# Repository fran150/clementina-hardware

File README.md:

# Clementina Hardware

KiCad 9 schematic and board for Clementina, a 3.3 V homebrew computer built
around a W65C02S CPU. A Raspberry Pi Pico 2 W, called MIA, runs the machine: it
generates the CPU clock, boots the kernel, and provides video, audio, storage
and input.

Status: the rev 1 schematic is complete and ERC-clean, and the rev 1 board is
laid out, fully routed and DRC-clean. The first build is planned on
protoboard, using the same parts as the board.

## Opening the project

Open `clementina-hardware.kicad_pro` in KiCad 9.

- `clementina.kicad_sym` (listed in `sym-lib-table`) holds the parts KiCad's
  own libraries lack, currently the AS6C62256 SRAM.
- The W65C02S and W65C22S symbols come from KiCad's Plugin and Content Manager
  (library `PCM_65xx-library`). The schematic carries copies, so it opens
  without that library. Install it to keep ERC's library check clean.
- One ERC item is excluded on purpose: the Pico's AGND tied to GND. The ADC is
  unused, and the Pico datasheet allows the join.
- `clementina-hardware.kicad_dru` holds one custom DRC rule: the audio jack's
  barrel hangs over the board edge on purpose, so its silkscreen outline may
  cross the edge.
- DRC shows one warning, and it is expected: the Pico footprint "does not
  match the copy in the library". The library's antenna keep-out lists 32
  copper layers, and a 2-layer board keeps only two of them.

Sheets:

| Sheet | Contents |
| --- | --- |
| `clementina-hardware.kicad_sch` (A3) | CPU, VIA, RAM, MIA, IRQ and reset circuits, expansion headers, user port, audio output, microSD, power and decoupling |
| `CS Logic.kicad_sch` | Address decoding (74AC138 x2, 74AC08, two gates of the 74AC00) |
| `OE_RW_PHI2_Sync.kicad_sch` | Read and write strobes: `~OE` from R/W, `~WE` qualified by PHI2 (two gates of the 74AC00) |

## Architecture

| Part | Role |
| --- | --- |
| W65C02S (U1) | CPU. MIA drives PHI2: 1.2 MHz by default, up to 8 MHz. |
| AS6C62256 (U4) | 32 KB base RAM |
| AS6C4008 (U2) | 512 KB extended RAM, seen through a 16 KB window |
| W65C22S (U3) | VIA. Port A selects the extended RAM bank; port B and CA/CB go to the user port. |
| Raspberry Pi Pico 2 W (A1) | MIA: clock, boot loader, video over Wi-Fi, audio, microSD, input, reset |
| 74AC138 x2, 74AC08, 74AC00 | Glue logic (see [Glue logic timing](#glue-logic-timing)) |

Memory map:

| Range | Device |
| --- | --- |
| `$0000-$7FFF` | Base RAM |
| `$8000-$BFFF` | Extended RAM window (32 banks, selected by VIA PA0-PA4) |
| `$C000-$DFFF` | I/O: eight 1 KB slots. Slot 0 (`$C000`) is the VIA; slots 1-7 go to the expansion headers. |
| `$E000-$FFFF` | MIA (registers at `$FFE0-$FFFF`) |

MIA's pins:

| GPIO | Signal |
| --- | --- |
| GP0-GP3 | microSD (SPI0: MISO, CS, SCK, MOSI) |
| GP4, GP5 | Audio left and right (PWM) |
| GP6 | MIA chip select |
| GP7 | R/W |
| GP8-GP15 | D0-D7 |
| GP16-GP20 | A0-A4 |
| GP21 | PHI2 |
| GP22 | IRQ |
| GP26 | RESB (MIA holds the CPU and VIA in reset) |
| GP27 | Reset request from the RESET button |
| GP28 | Unused |

### Glue logic timing

The glue logic is 74AC, not 74HC, because 74HC is slow at 3.3 V (roughly
13 ns per gate typical, up to about 30 ns). Two places depend on it:

- **Write strobe.** `~WE = NAND(PHI2, ~OE)` in one 74AC00 gate, so `~WE`
  rises within about 10 ns of PHI2 falling. The W65C02S only guarantees its
  address and data for 10 ns after PHI2 falls, and the SRAMs need both held
  until `~WE` rises. This timing doesn't depend on clock speed, so running
  slower doesn't help. The Picocomputer RP6502 makes WE# the same way.
- **Chip selects.** The VIA and the expansion cards need their chip select
  10 ns before PHI2 rises. U6 is enabled straight from A13-A15 (A15
  through one inverting gate), not through U8, which removes a decoder level
  from those selects.

With 74AC parts, the chip-select paths meet the datasheets up to about
6.5 MHz with worst-case parts, and typical parts reach 8 MHz. 74HC parts give
the same logic but lose the write-strobe guarantee, and the VIA's chip select
limits them to about 3.5 MHz worst case.

Interrupts are wired-AND: MIA and the VIA each pull `~IRQB` low through a BAT85
Schottky diode against a 4.7 kΩ pull-up. `~NMI` (4.7 kΩ) and RDY (2.2 kΩ) are
also pulled up, so expansion cards can use them. RDY is also an output: the
CPU pulls it low while it executes `WAI`. The W65C02S only guarantees 1.6 mA
at 0.4 V there, so the RDY pull-up can't be stronger than about 2 kΩ.

## Power (rev 1)

Everything runs from the Pico's USB. Its 3V3 output supplies the whole board,
and VBUS supplies the `+5V` pins on the headers.

- Keep the external 3.3 V load under about 300 mA. The board uses roughly
  50 mA idle and 150 mA with the microSD card writing, which leaves about
  150 mA for expansion cards.
- A phone charger works when no PC is attached.
- VSYS is left free for a rev 2 power input.

## Connectors

**J1, J2: expansion bus** (2x20 keyed box headers, identical)

| Pin | Signal | Pin | Signal |
| ---: | --- | ---: | --- |
| 1 | GND | 2 | +3.3V |
| 3 | A0 | 4 | A1 |
| 5 | A2 | 6 | A3 |
| 7 | A4 | 8 | A5 |
| 9 | A6 | 10 | A7 |
| 11 | A8 | 12 | A9 |
| 13 | GND | 14 | PHI2 |
| 15 | GND | 16 | RWB |
| 17 | ~OE | 18 | ~WE |
| 19 | ~RESB | 20 | ~IRQB |
| 21 | ~NMI | 22 | RDY |
| 23 | D0 | 24 | D1 |
| 25 | D2 | 26 | D3 |
| 27 | D4 | 28 | D5 |
| 29 | D6 | 30 | D7 |
| 31 | ~IOCS1 | 32 | ~IOCS2 |
| 33 | ~IOCS3 | 34 | ~IOCS4 |
| 35 | ~IOCS5 | 36 | ~IOCS6 |
| 37 | ~IOCS7 | 38 | +5V |
| 39 | GND | 40 | +3.3V |

**J3: user port** (2x10 keyed box header, VIA port B)

| Pin | Signal | Pin | Signal |
| ---: | --- | ---: | --- |
| 1 | GND | 2 | +3.3V |
| 3 | PB0 | 4 | PB1 |
| 5 | PB2 | 6 | PB3 |
| 7 | PB4 | 8 | PB5 |
| 9 | PB6 | 10 | PB7 |
| 11 | CB1 | 12 | CB2 |
| 13 | CA1 | 14 | CA2 |
| 15 | ~RESB | 16 | GND |
| 17 | GND | 18 | +5V |
| 19 | GND | 20 | +3.3V |

Rules for cards on J1-J3:

- 3.3 V logic only. Never put a 5 V signal on any pin.
- A card claims one I/O slot by jumpering one of `~IOCS1`-`~IOCS7`.
- `~IRQB`, `~NMI` and RDY: pull them low through a Schottky diode or an
  open-drain output, and never drive them high.
- RDY also goes low while the CPU executes `WAI`. Don't read RDY low as a
  wait request from another card.
- `~RESB` is driven by MIA: read it, never drive it.
- W65C22S port pins have no current limiting. Drive LEDs and similar loads
  through a resistor.

**J4: audio out.** A stereo 3.5 mm jack (CUI SJ1-3533NG, through-hole, round
pins): tip left, ring right. Each channel
uses the same output stage as the Picocomputer RP6502: a 220 Ω / 100 Ω
divider, a 100 nF filter capacitor, a 47 µF DC block and a 1.8 kΩ bleed
resistor. It gives about 1 Vpp line level and drives headphones directly. MIA
mixes at 48 kHz.

**J5: microSD.** A 1x9 female header for the Adafruit 4682 microSD breakout
(3 V only), used in SPI mode on MIA's SPI0: 400 kHz to initialise, then
12 MHz. The breakout has its own pull-ups (CS, MISO, DAT1, DAT2) and bypass
capacitors. DAT1, DAT2 and card detect stay unconnected.

| Pin | 1 | 2 | 3 | 4 | 5 | 6 | 7 | 8 | 9 |
| --- | --- | --- | --- | --- | --- | --- | --- | --- | --- |
| Breakout | 3V | GND | CLK | SO | SI | CS | DAT1 | DAT2 | DET |
| Signal | +3.3V | GND | SD_SCK | SD_MISO | SD_MOSI | SD_CS | - | - | - |

## Board (rev 1)

`clementina-hardware.kicad_pcb`: 172.7 x 108.6 mm, 2 layers, every part
through-hole. The chips sit in sockets and the Pico plugs into female headers,
so the same parts move from the protoboard build to the board.

- Layout: the MIA Pico is at the top left, with its USB port on the top edge
  and its Wi-Fi antenna over a copper keep-out. The microSD breakout sits to
  its left, with the card slot at the left board edge. The audio stage and jack
  run down the left edge, and the reset button sits well below the Pico. The CPU,
  RAM, extended RAM and VIA form one row, with the user port at the right edge.
  The glue logic is in a row below them, and the two expansion headers are
  stacked along the bottom edge.
- Every chip has a 100 nF capacitor next to its supply pin; C14 (22 µF) is by
  the Pico's 3V3 pin.
- Wi-Fi antenna: Raspberry Pi recommends putting the Pico W's antenna at a
  board edge with nothing close to it. Here it sits inside the board, as on the
  Picocomputer RP6502. The Pico stands about 10 mm up on its headers, no copper
  runs under the antenna, and a rule area ("Wi-Fi antenna clearance") keeps
  tracks, vias and ground fill about 6 mm past the Pico's end. Leave that area
  clear of parts and cables. The expected cost is a few dB of range, which the
  video protocol tolerates. To check a build, compare the Wi-Fi signal
  strength (RSSI) of the Pico on its own and on the board at the same spot; if
  the board costs more than about 6 dB, move the antenna to an edge in rev 2.
- Routing: 0.25 mm signal tracks, 0.4 mm for GND, +3.3V and +5V (net class
  `Power`), 0.2 mm clearance, and 0.6 / 0.3 mm vias. The top layer runs mostly
  horizontal and the bottom mostly vertical. Both layers carry a GND pour,
  stitched with vias. Any hobby PCB fab can make it (1.6 mm FR-4, 1 oz copper).
- The routing was produced by a script and then checked with KiCad's DRC and
  its schematic parity check. Edit it freely in KiCad.
- Silkscreen: part values are printed on the resistors and capacitors, and the
  chip names inside the socket outlines. The J5 pin names and the breakout's
  outline are printed too.
- Mounting: four M3 holes in the corners. Two M2.5 holes under the microSD
  breakout match its own holes. They're optional, to support it with
  standoffs (about 11 mm).

### Bill of materials

Every part has two schematic fields that keep the bill of materials generic,
so you can source parts yourself (for the protoboard build) or hand them to an
assembly service:

- **Factory**: what gets soldered to the board at that designator. Chips get a
  DIP socket, and the Pico (A1) gets two 1x20 female headers.
- **Plug-in**: what you plug in afterwards, if anything.

[`bom/factory-bom.csv`](bom/factory-bom.csv) lists everything that's
soldered: passives, diodes, sockets, headers, the jack and the button. With
those soldered (by you or the factory), the board needs no more soldering;
plug in these parts:

| Ref | Part |
| --- | --- |
| U1 | WDC W65C02S CPU, DIP-40 (W65C02S6TPG-14) |
| U3 | WDC W65C22S VIA, DIP-40 (W65C22S6TPG-14) |
| U4 | Alliance AS6C62256-55PCN, 32K x 8 SRAM, DIP-28 |
| U2 | Alliance AS6C4008-55PCN, 512K x 8 SRAM, DIP-32 |
| U6, U8 | 74AC138, DIP-16 |
| U7 | 74AC08, DIP-14 |
| U9 | 74AC00, DIP-14 |
| A1 | Raspberry Pi Pico 2 WH (the version with pins already soldered) |
| J5 | Adafruit 4682 microSD breakout, 3 V |

The Adafruit 4682 ships with its header loose: solder the 9 pins to the
module once, or use a breakout sold with the header fitted.

The "A1" row of the factory BOM is two headers, one per side of the Pico.

To regenerate the factory BOM after changing parts:

```
kicad-cli sch export bom --fields 'Factory,${QUANTITY},Reference' --labels 'Part,Qty,References' --group-by Factory --sort-field Reference --sort-asc -o bom/factory-bom.csv clementina-hardware.kicad_sch
```

### Fabrication files

The Gerbers are generated from the board, so they aren't committed: git
ignores `fabrication/`. Rebuild them after any board change:

```
mkdir -p fabrication/gerbers
kicad-cli pcb export gerbers --no-x2 --no-netlist --subtract-soldermask -l F.Cu,B.Cu,F.Mask,B.Mask,F.Silkscreen,Edge.Cuts -o fabrication/gerbers/ clementina-hardware.kicad_pcb
kicad-cli pcb export drill --excellon-separate-th -o fabrication/gerbers/ clementina-hardware.kicad_pcb
rm fabrication/gerbers/*.gbrjob
zip -j -FS fabrication/clementina-rev1-gerbers.zip fabrication/gerbers/*
```

Upload `fabrication/clementina-rev1-gerbers.zip` to the fab. It holds eight
files: both copper layers, both masks, the front silkscreen, the board outline,
and separate drill files for plated and unplated holes.

- `--no-x2 --no-netlist`: PCBWay's KiCad guide asks for Gerbers without X2
  attributes. With them, its upload preview showed only the holes.
- No back silkscreen: it's empty.
- `--subtract-soldermask` keeps silkscreen ink off the pads.
- The zip leaves out KiCad's `.gbrjob` job file.
- `zip -FS` also removes files that are no longer in `fabrication/gerbers/`.

When you order boards, tag the commit you ordered from and attach the zip you
uploaded to a GitHub release on that tag. That keeps a record of exactly what
was made.

## Not in rev 1

- A separate power input (USB-C into VSYS) with a jumper to power a USB
  keyboard on the Pico's port
- Local video output, likely a second Pico as a display client

## Related repositories

- [clementina-6502](https://github.com/fran150/clementina-6502): emulator
- [clementina-mia](https://github.com/fran150/clementina-mia): MIA firmware
- [clementina-rom](https://github.com/fran150/clementina-rom): kernel,
  BASIC and WozMon
- [clementina-sdk](https://github.com/fran150/clementina-sdk): development SDK
- [clementina-studio](https://github.com/fran150/clementina-studio): asset
  editor
- [clementina-video-client](https://github.com/fran150/clementina-video-client):
  video client

## License

GPLv3. See [LICENSE](LICENSE).

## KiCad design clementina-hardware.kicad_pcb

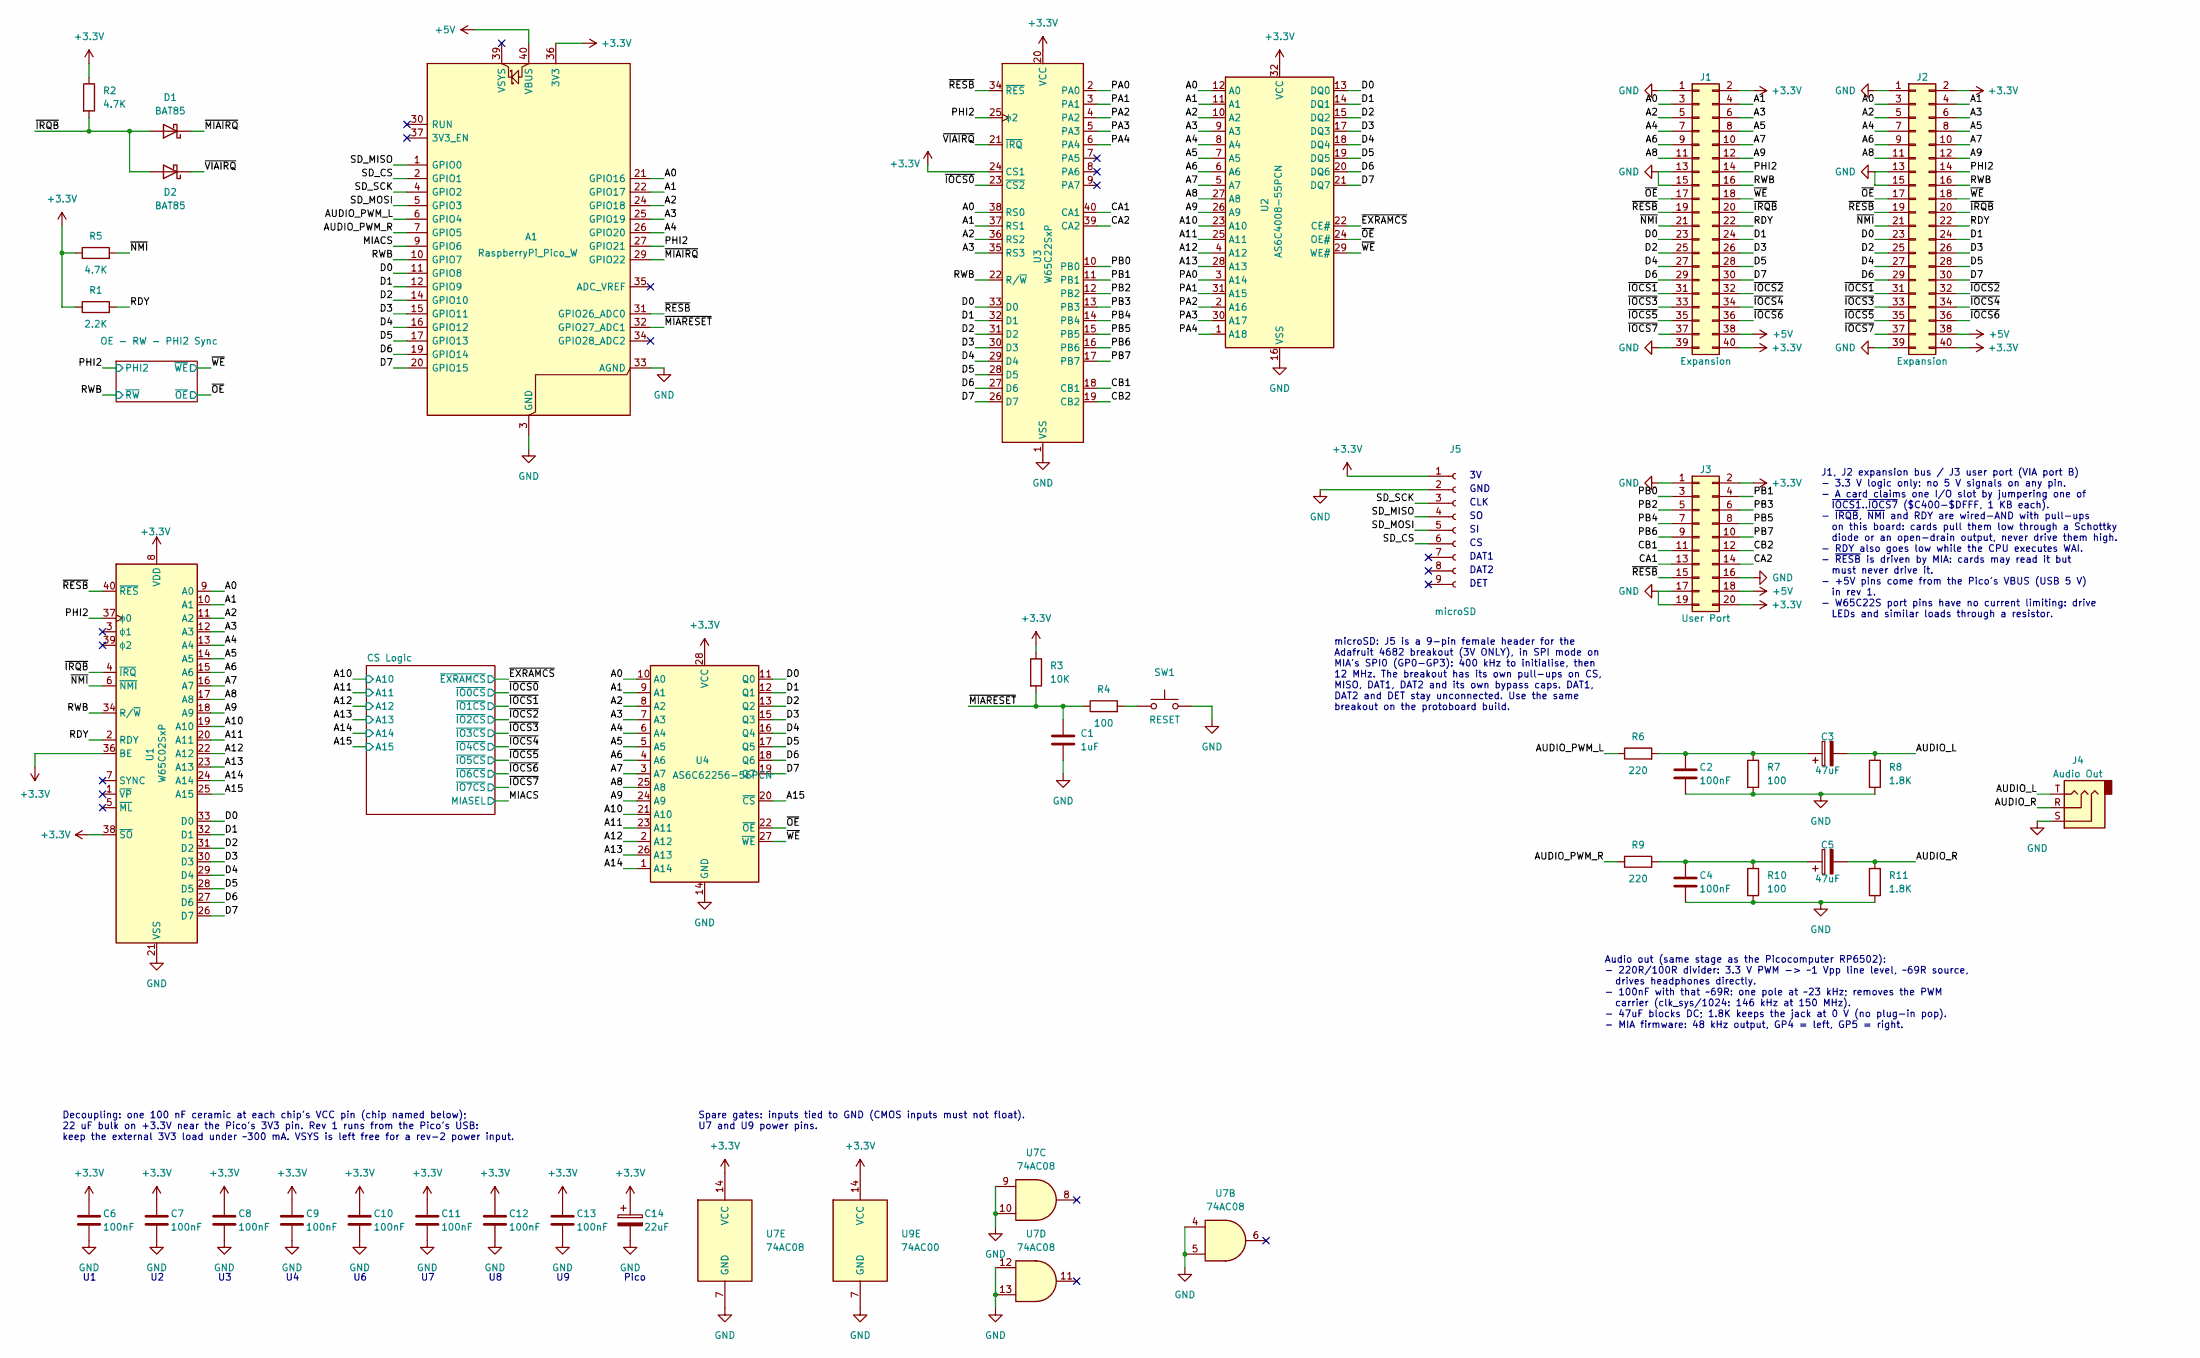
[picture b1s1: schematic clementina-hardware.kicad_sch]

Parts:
A1: RaspberryPi_Pico_W; RaspberryPi_Pico_Common_THT
C1: 1uF; C_Disc_D5.0mm_W2.5mm_P5.00mm
C2, C4, C6, C7, C8, C9, C10, C11, C12, C13: 100nF; C_Disc_D5.0mm_W2.5mm_P5.00mm
C3, C5: 47uF; CP_Radial_D5.0mm_P2.50mm
C14: 22uF; CP_Radial_D5.0mm_P2.50mm
D1, D2: BAT85; D_DO-34_SOD68_P7.62mm_Horizontal
J1, J2: Expansion; IDC-Header_2x20_P2.54mm_Vertical
J3: User Port; IDC-Header_2x10_P2.54mm_Vertical
J4: Audio Out; Jack_3.5mm_CUI_SJ1-3533NG_Horizontal_CircularHoles
J5: microSD; PinSocket_1x09_P2.54mm_Vertical
R1: 2.2K; R_Axial_DIN0207_L6.3mm_D2.5mm_P10.16mm_Horizontal
R2, R5: 4.7K; R_Axial_DIN0207_L6.3mm_D2.5mm_P10.16mm_Horizontal
R3: 10K; R_Axial_DIN0207_L6.3mm_D2.5mm_P10.16mm_Horizontal
R4, R7, R10: 100; R_Axial_DIN0207_L6.3mm_D2.5mm_P10.16mm_Horizontal
R6, R9: 220; R_Axial_DIN0207_L6.3mm_D2.5mm_P10.16mm_Horizontal
R8, R11: 1.8K; R_Axial_DIN0207_L6.3mm_D2.5mm_P10.16mm_Horizontal
SW1: RESET; SW_PUSH_6mm
U1: W65C02SxP; DIP-40_W15.24mm_Socket
U2: AS6C4008-55PCN; DIP-32_W15.24mm_Socket
U3: W65C22SxP; DIP-40_W15.24mm_Socket
U4: AS6C62256-55PCN; DIP-28_W15.24mm_Socket
U7: 74AC08; DIP-14_W7.62mm_Socket
U9: 74AC00; DIP-14_W7.62mm_Socket

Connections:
+3.3V: A1.36 (3V3), C6.1, C7.1, C8.1, C9.1, C10.1, C11.1, C12.1, C13.1, C14.1, J1.2, J1.40, J2.2, J2.40, J3.2, J3.20, J5.1, R1.1, R2.1, R3.1, R5.1, U1.8 (VDD), U1.36 (BE), U1.38 (~SO), U2.32 (VCC), U3.20 (VCC), U3.24 (CS1), U4.28 (VCC), U7.14 (VCC), U9.14 (VCC); also elsewhere on the board
+5V: A1.40 (VBUS), J1.38, J2.38, J3.18
/A0: A1.21 (GPIO16), J1.3, J2.3, U1.9 (A0), U2.12 (A0), U3.38 (RS0), U4.10 (A0)
/A1: A1.22 (GPIO17), J1.4, J2.4, U1.10 (A1), U2.11 (A1), U3.37 (RS1), U4.9 (A1)
/A2: A1.24 (GPIO18), J1.5, J2.5, U1.11 (A2), U2.10 (A2), U3.36 (RS2), U4.8 (A2)
/A3: A1.25 (GPIO19), J1.6, J2.6, U1.12 (A3), U2.9 (A3), U3.35 (RS3), U4.7 (A3)
/A4: A1.26 (GPIO20), J1.7, J2.7, U1.13 (A4), U2.8 (A4), U4.6 (A4)
/A5: J1.8, J2.8, U1.14 (A5), U2.7 (A5), U4.5 (A5)
/A6: J1.9, J2.9, U1.15 (A6), U2.6 (A6), U4.4 (A6)
/A7: J1.10, J2.10, U1.16 (A7), U2.5 (A7), U4.3 (A7)
/A8: J1.11, J2.11, U1.17 (A8), U2.27 (A8), U4.25 (A8)
/A9: J1.12, J2.12, U1.18 (A9), U2.26 (A9), U4.24 (A9)
/A10: U1.19 (A10), U2.23 (A10), U4.21 (A10); also elsewhere on the board
/A11: U1.20 (A11), U2.25 (A11), U4.23 (A11); also elsewhere on the board
/A12: U1.22 (A12), U2.4 (A12), U4.2 (A12); also elsewhere on the board
/A13: U1.23 (A13), U2.28 (A13), U4.26 (A13); also elsewhere on the board
/A14: U1.24 (A14), U4.1 (A14); also elsewhere on the board
/A15: U1.25 (A15), U4.20 (~CS); also elsewhere on the board
/AUDIO_L: C3.2, J4.T, R8.1
/AUDIO_PWM_L: A1.6 (GPIO4), R6.1
/AUDIO_PWM_R: A1.7 (GPIO5), R9.1
/AUDIO_R: C5.2, J4.R, R11.1
/CA1: J3.13, U3.40 (CA1)
/CA2: J3.14, U3.39 (CA2)
/CB1: J3.11, U3.18 (CB1)
/CB2: J3.12, U3.19 (CB2)
/D0: A1.11 (GPIO8), J1.23, J2.23, U1.33 (D0), U2.13 (DQ0), U3.33 (D0), U4.11 (Q0)
/D1: A1.12 (GPIO9), J1.24, J2.24, U1.32 (D1), U2.14 (DQ1), U3.32 (D1), U4.12 (Q1)
/D2: A1.14 (GPIO10), J1.25, J2.25, U1.31 (D2), U2.15 (DQ2), U3.31 (D2), U4.13 (Q2)
/D3: A1.15 (GPIO11), J1.26, J2.26, U1.30 (D3), U2.17 (DQ3), U3.30 (D3), U4.15 (Q3)
/D4: A1.16 (GPIO12), J1.27, J2.27, U1.29 (D4), U2.18 (DQ4), U3.29 (D4), U4.16 (Q4)
/D5: A1.17 (GPIO13), J1.28, J2.28, U1.28 (D5), U2.19 (DQ5), U3.28 (D5), U4.17 (Q5)
/D6: A1.19 (GPIO14), J1.29, J2.29, U1.27 (D6), U2.20 (DQ6), U3.27 (D6), U4.18 (Q6)
/D7: A1.20 (GPIO15), J1.30, J2.30, U1.26 (D7), U2.21 (DQ7), U3.26 (D7), U4.19 (Q7)
/MIACS: A1.9 (GPIO6); also elsewhere on the board
/PA0: U2.3 (A14), U3.2 (PA0)
/PA1: U2.31 (A15), U3.3 (PA1)
/PA2: U2.2 (A16), U3.4 (PA2)
/PA3: U2.30 (A17), U3.5 (PA3)
/PA4: U2.1 (A18), U3.6 (PA4)
/PB0: J3.3, U3.10 (PB0)
/PB1: J3.4, U3.11 (PB1)
/PB2: J3.5, U3.12 (PB2)
/PB3: J3.6, U3.13 (PB3)
/PB4: J3.7, U3.14 (PB4)
/PB5: J3.8, U3.15 (PB5)
/PB6: J3.9, U3.16 (PB6)
/PB7: J3.10, U3.17 (PB7)
/PHI2: A1.27 (GPIO21), J1.14, J2.14, U1.37 (ϕ0), U3.25 (ϕ2); also elsewhere on the board
/RDY: J1.22, J2.22, R1.2, U1.2 (RDY)
/RWB: A1.10 (GPIO7), J1.16, J2.16, U1.34 (R/~W), U3.22 (R/~W); also elsewhere on the board
/SD_CS: A1.2 (GPIO1), J5.6
/SD_MISO: A1.1 (GPIO0), J5.4
/SD_MOSI: A1.5 (GPIO3), J5.5
/SD_SCK: A1.4 (GPIO2), J5.3
/~EXRAMCS: U2.22 (CE#); also elsewhere on the board
/~IOCS0: U3.23 (~CS2); also elsewhere on the board
/~IOCS1: J1.31, J2.31; also elsewhere on the board
/~IOCS2: J1.32, J2.32; also elsewhere on the board
/~IOCS3: J1.33, J2.33; also elsewhere on the board
/~IOCS4: J1.34, J2.34; also elsewhere on the board
/~IOCS5: J1.35, J2.35; also elsewhere on the board
/~IOCS6: J1.36, J2.36; also elsewhere on the board
/~IOCS7: J1.37, J2.37; also elsewhere on the board
/~IRQB: D1.2 (A), D2.2 (A), J1.20, J2.20, R2.2, U1.4 (~IRQ)
/~MIAIRQ: A1.29 (GPIO22), D1.1 (K)
/~MIARESET: A1.32 (GPIO27_ADC1), C1.1, R3.2, R4.1
/~NMI: J1.21, J2.21, R5.2, U1.6 (~NMI)
/~OE: J1.17, J2.17, U2.24 (OE#), U4.22 (~OE); also elsewhere on the board
/~RESB: A1.31 (GPIO26_ADC0), J1.19, J2.19, J3.15, U1.40 (~RES), U3.34 (~RES)
/~VIAIRQ: D2.1 (K), U3.21 (~IRQ)
/~WE: J1.18, J2.18, U2.29 (WE#), U4.27 (~WE); also elsewhere on the board
GND: A1.3 (GND), A1.8 (GND), A1.13 (GND), A1.18 (GND), A1.23 (GND), A1.28 (GND), A1.33 (AGND), A1.38 (GND), C1.2, C2.2, C4.2, C6.2, C7.2, C8.2, C9.2, C10.2, C11.2, C12.2, C13.2, C14.2, J1.1, J1.13, J1.15, J1.39, J2.1, J2.13, J2.15, J2.39, J3.1, J3.16, J3.17, J3.19, J4.S, J5.2, R7.2, R8.2, R10.2, R11.2, SW1.2, U1.21 (VSS), U2.16 (VSS), U3.1 (VSS), U4.14 (GND), U7.4, U7.5, U7.7 (GND), U7.9, U7.10, U7.12, U7.13, U9.7 (GND); also elsewhere on the board
unnamed: C2.1, C3.1, R6.2, R7.1
unnamed: C4.1, C5.1, R9.2, R10.1
unnamed: R4.2, SW1.1

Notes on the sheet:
GND
CLK
DAT1
DAT2
DET
microSD: J5 is a 9-pin female header for the Adafruit 4682 breakout (3V ONLY), in SPI mode on MIA's SPI0 (GP0-GP3): 400 kHz to initialise, then 12 MHz. The breakout has its own pull-ups on CS, MISO, DAT1, DAT2 and its own bypass caps. DAT1, DAT2 and DET stay unconnected. Use the same breakout on th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
Spare gates: inputs tied to GND (CMOS inputs must not float). U7 and U9 power pins.
Pico
Decoupling: one 100 nF ceramic at each chip's VCC pin (chip named below); 22 uF bulk on +3.3V near the Pico's 3V3 pin. Rev 1 runs from the Pico's USB: keep the external 3V3 load under ~300 mA. VSYS is left free for a rev-2 power input.
Audio out (same stage as the Picocomputer RP6502): - 220R/100R divider: 3.3 V PWM -> ~1 Vpp line level, ~69R source, drives headphones directly. - 100nF with that ~69R: one pole at ~23 kHz; removes the PWM carrier (clk_sys/1024: 146 kHz at 150 MHz). - 47uF blocks DC; 1.8K keeps the jack at 0 V (no 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
J1, J2 expansion bus / J3 user port (VIA port B) - 3.3 V logic only: no 5 V signals on any pin. - A card claims one I/O slot by jumpering one of ~{IOCS1}..~{IOCS7} ($C400-$DFFF, 1 KB each). - ~{IRQB}, ~{NMI} and RDY are wired-AND with pull-ups on this board: cards pull them low through a Schottky d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

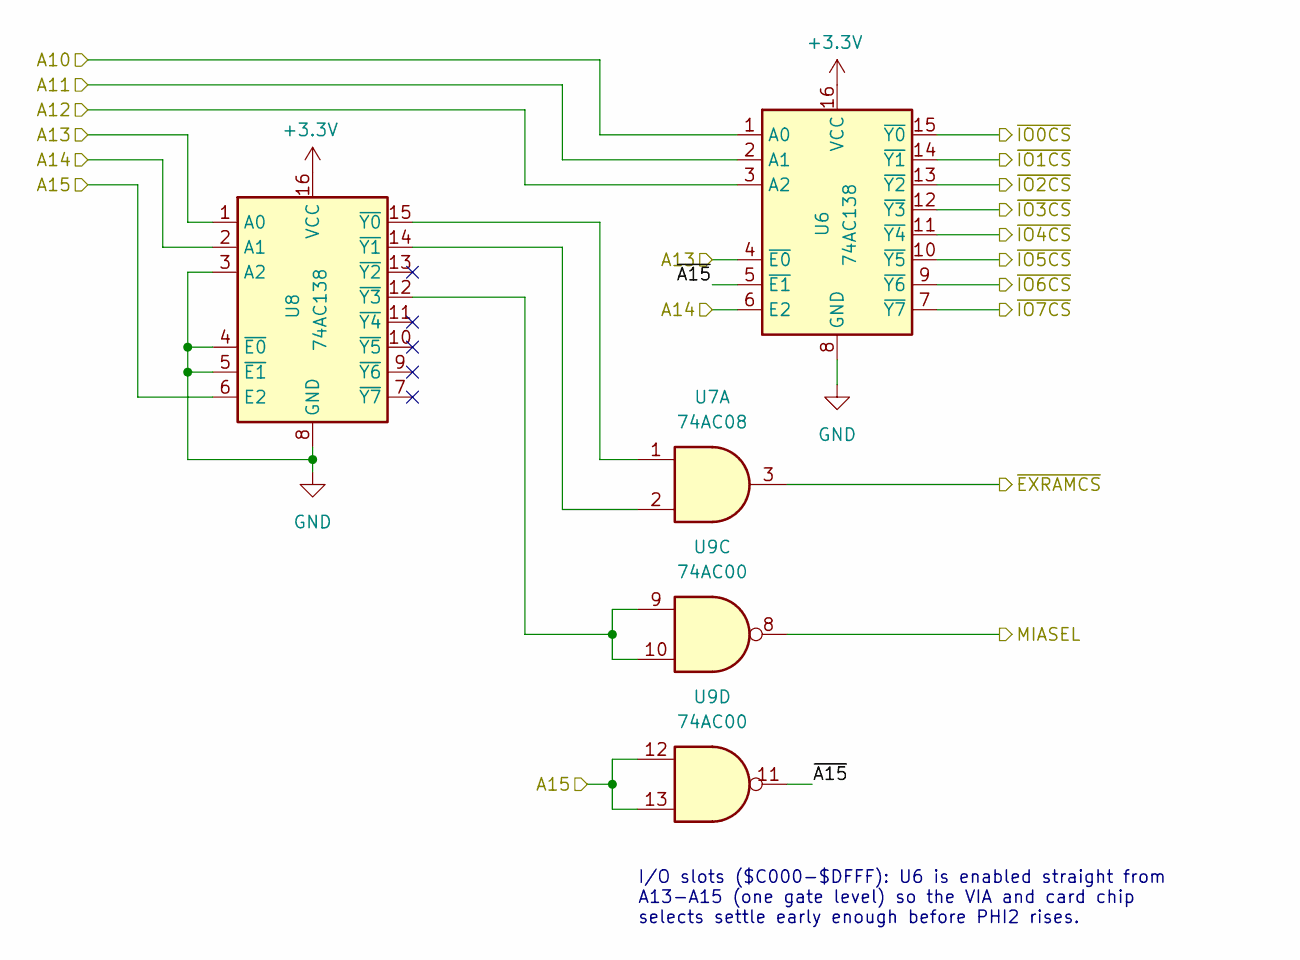
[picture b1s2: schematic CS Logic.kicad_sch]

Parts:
U6, U8: 74AC138; DIP-16_W7.62mm_Socket
U7: 74AC08; DIP-14_W7.62mm_Socket
U9: 74AC00; DIP-14_W7.62mm_Socket

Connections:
+3.3V: U6.16 (VCC), U8.16 (VCC); also elsewhere on the board
/A10: U6.1 (A0); also elsewhere on the board
/A11: U6.2 (A1); also elsewhere on the board
/A12: U6.3 (A2); also elsewhere on the board
/A13: U6.4 (~E0), U8.1 (A0); also elsewhere on the board
/A14: U6.6 (E2), U8.2 (A1); also elsewhere on the board
/A15: U8.6 (E2), U9.12, U9.13; also elsewhere on the board
/CS Logic/~A15: U6.5 (~E1), U9.11
/MIACS: U9.8; also elsewhere on the board
/~EXRAMCS: U7.3; also elsewhere on the board
/~IOCS0: U6.15 (~Y0); also elsewhere on the board
/~IOCS1: U6.14 (~Y1); also elsewhere on the board
/~IOCS2: U6.13 (~Y2); also elsewhere on the board
/~IOCS3: U6.12 (~Y3); also elsewhere on the board
/~IOCS4: U6.11 (~Y4); also elsewhere on the board
/~IOCS5: U6.10 (~Y5); also elsewhere on the board
/~IOCS6: U6.9 (~Y6); also elsewhere on the board
/~IOCS7: U6.7 (~Y7); also elsewhere on the board
GND: U6.8 (GND), U8.3 (A2), U8.4 (~E0), U8.5 (~E1), U8.8 (GND); also elsewhere on the board
unnamed: U7.1, U8.15 (~Y0)
unnamed: U7.2, U8.14 (~Y1)
unnamed: U8.12 (~Y3), U9.9, U9.10

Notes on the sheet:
I/O slots ($C000-$DFFF): U6 is enabled straight from A13-A15 (one gate level) so the VIA and card chip selects settle early enough before PHI2 rises.

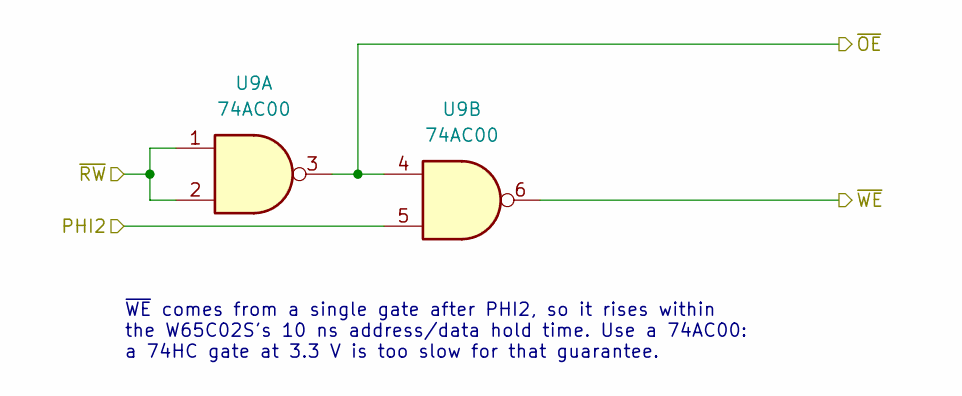
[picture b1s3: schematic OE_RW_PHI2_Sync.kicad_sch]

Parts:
U9: 74AC00; DIP-14_W7.62mm_Socket

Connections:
/PHI2: U9.5; also elsewhere on the board
/RWB: U9.1, U9.2; also elsewhere on the board
/~OE: U9.3, U9.4; also elsewhere on the board
/~WE: U9.6; also elsewhere on the board

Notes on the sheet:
~{WE} comes from a single gate after PHI2, so it rises within the W65C02S's 10 ns address/data hold time. Use a 74AC00: a 74HC gate at 3.3 V is too slow for that guarantee.

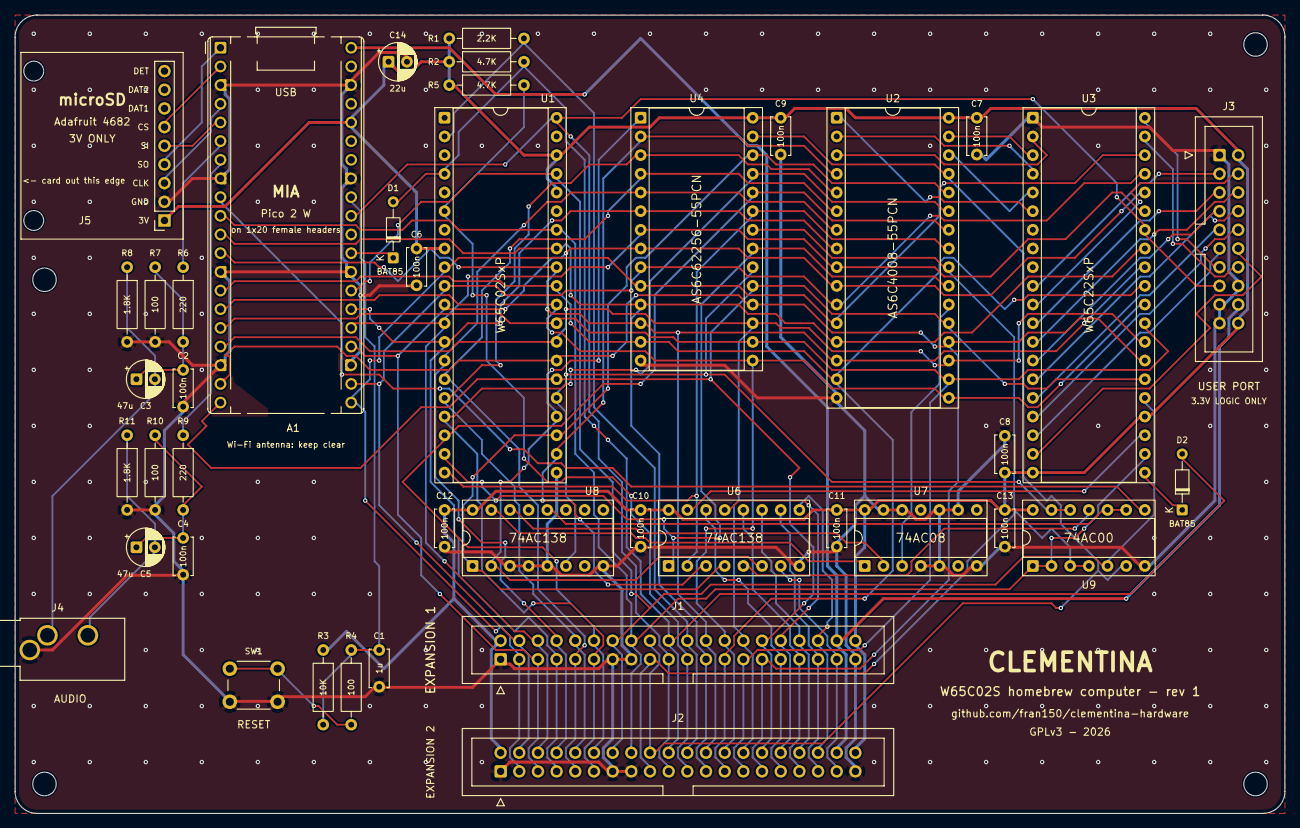
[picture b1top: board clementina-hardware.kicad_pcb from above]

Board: 2 copper layers, 172.7 x 108.6 mm, 48 parts (0 on the bottom side), 80 nets.

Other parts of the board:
H1, H2, H3, H4: MountingHole_3.2mm_M3
H5, H6: MountingHole_2.7mm_M2.5

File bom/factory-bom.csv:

"Part","Qty","References"
"2 x female header 1x20, 2.54 mm, 8.5 mm tall (both at A1, one per Pico side)","1","A1"
"Ceramic capacitor 1 µF, 50 V, X7R, radial, 5.08 mm lead spacing","1","C1"
"Electrolytic capacitor 22 µF, 16 V, radial, 5 mm diameter, 2.5 mm lead spacing","1","C14"
"Ceramic capacitor 100 nF, 50 V, X7R, radial, 5.08 mm lead spacing","10","C2,C4,C6-C13"
"Electrolytic capacitor 47 µF, 16 V, radial, 5 mm diameter, 2.5 mm lead spacing","2","C3,C5"
"BAT85 Schottky diode, DO-34","2","D1,D2"
"IDC box header 2x10, 2.54 mm, vertical","1","J3"
"3.5 mm stereo jack, CUI SJ1-3533NG or same footprint","1","J4"
"Female header 1x9, 2.54 mm, 8.5 mm tall","1","J5"
"IDC box header 2x20, 2.54 mm, vertical","2","J1,J2"
"Resistor 2.2 kΩ, 1/4 W, 1% metal film, axial, 10.16 mm lead spacing","1","R1"
"Resistor 10 kΩ, 1/4 W, 1% metal film, axial, 10.16 mm lead spacing","1","R3"
"Resistor 4.7 kΩ, 1/4 W, 1% metal film, axial, 10.16 mm lead spacing","2","R2,R5"
"Resistor 100 Ω, 1/4 W, 1% metal film, axial, 10.16 mm lead spacing","3","R4,R7,R10"
"Resistor 220 Ω, 1/4 W, 1% metal film, axial, 10.16 mm lead spacing","2","R6,R9"
"Resistor 1.8 kΩ, 1/4 W, 1% metal film, axial, 10.16 mm lead spacing","2","R8,R11"
"Tactile switch 6 x 6 mm, through-hole","1","SW1"
"DIP-32 socket, 15.24 mm (0.6 in) rows","1","U2"
"DIP-28 socket, 15.24 mm (0.6 in) rows","1","U4"
"DIP-40 socket, 15.24 mm (0.6 in) rows","2","U1,U3"
"DIP-16 socket, 7.62 mm (0.3 in) rows","2","U6,U8"
"DIP-14 socket, 7.62 mm (0.3 in) rows","2","U7,U9"

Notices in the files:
clementina-hardware.kicad_pcb:
GPLv3 - 2026
